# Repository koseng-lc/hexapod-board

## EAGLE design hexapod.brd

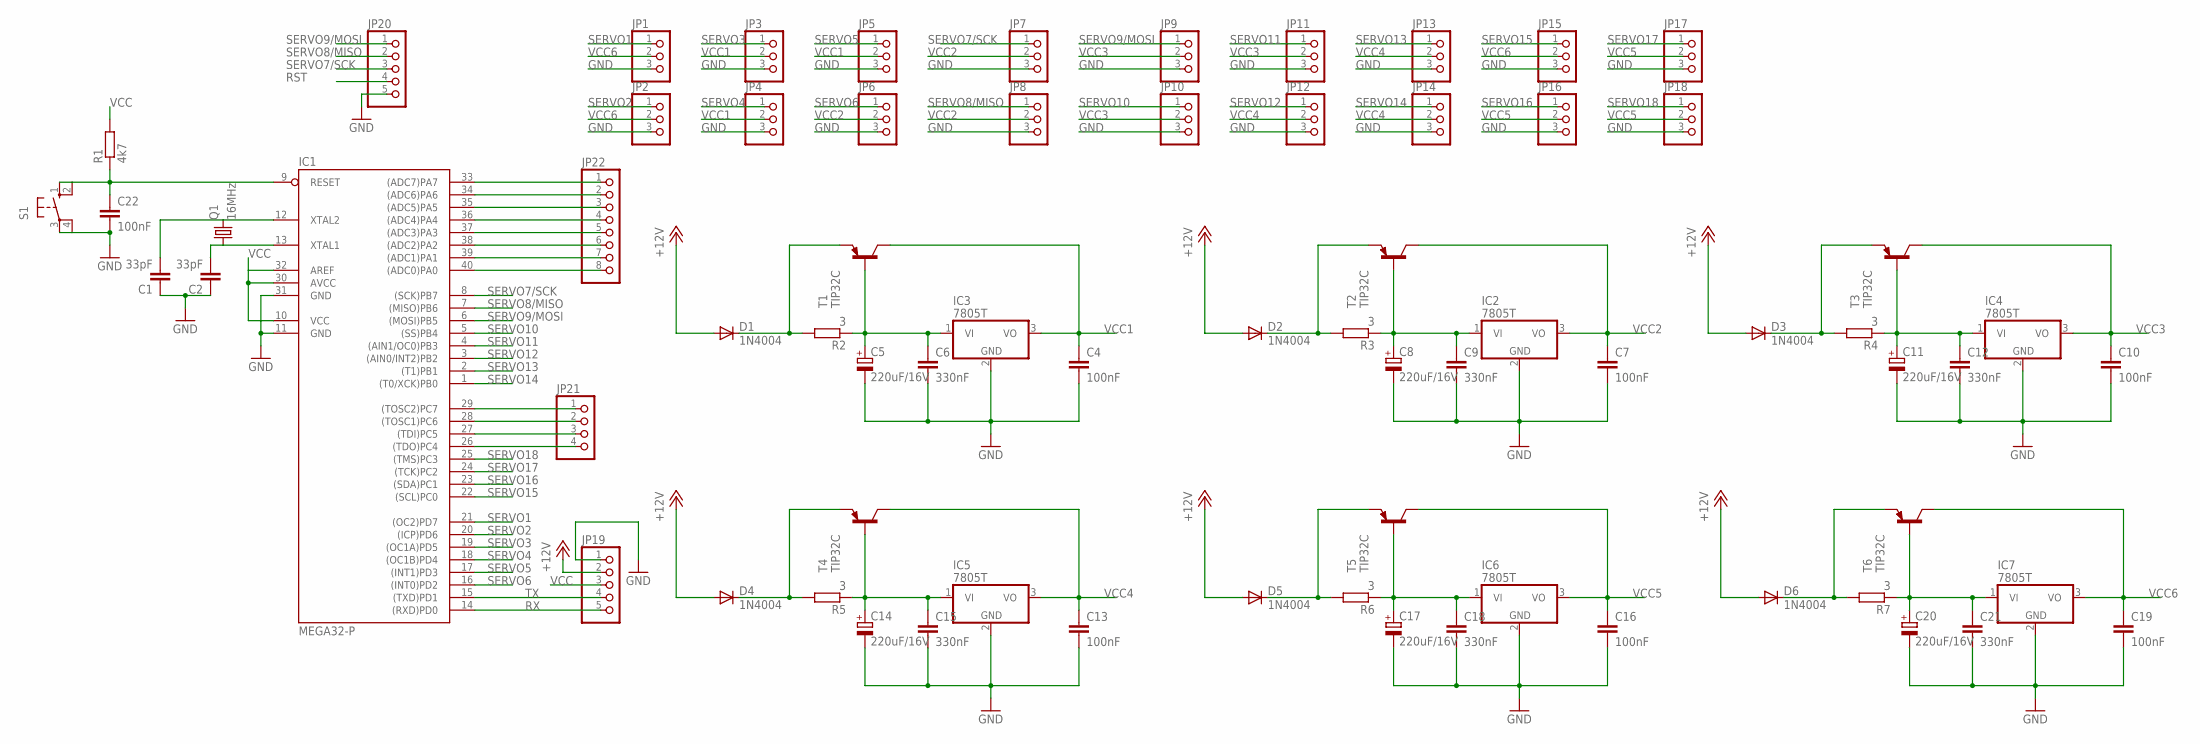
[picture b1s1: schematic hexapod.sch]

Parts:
C1, C2: 33pF; C025-025X050
C4, C7, C10, C13, C16, C19, C22: 100nF; C050-025X075
C5, C8, C11, C14, C17, C20: 220uF/16V; E2,5-6E
C6, C9, C12, C15, C18, C21: 330nF; C050-025X075
D1, D2, D3, D4, D5, D6: 1N4004; DO41-10
IC1: MEGA32-P; DIL40
IC2, IC3, IC4, IC5, IC6, IC7: 7805T; TO220H
JP1, JP2, JP3, JP4, JP5, JP6, JP7, JP8, JP9, JP10, JP11, JP12, JP13, JP14, JP15, JP16, JP17, JP18: PINHD-1X3; 1X03
JP19, JP20: PINHD-1X5; 1X05
JP21: PINHD-1X4; 1X04
JP22: PINHD-1X8; 1X08
Q1: 16MHz; HC49/S
R1: 4k7; 0204/7
R2, R3, R4, R5, R6, R7: 3; 0204/7
S1: 10-XX; B3F-10XX
T1, T2, T3, T4, T5, T6: TIP32C; TO220

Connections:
+12V: D1.A, D2.A, D3.A, D4.A, D5.A, D6.A, JP19.2
GND: C1.1, C2.1, C4.2, C5.-, C6.2, C7.2, C8.-, C9.2, C10.2, C11.-, C12.2, C13.2, C14.-, C15.2, C16.2, C17.-, C18.2, C19.2, C20.-, C21.2, C22.2, IC1.11 (GND), IC1.31 (GND), IC2.2 (GND), IC3.2 (GND), IC4.2 (GND), IC5.2 (GND), IC6.2 (GND), IC7.2 (GND), JP1.3, JP2.3, JP3.3, JP4.3, JP5.3, JP6.3, JP7.3, JP8.3, JP9.3, JP10.3, JP11.3, JP12.3, JP13.3, JP14.3, JP15.3, JP16.3, JP17.3, JP18.3, JP19.1, JP20.5, S1.3, S1.4 (P1)
unnamed: C1.2, IC1.12 (XTAL2), Q1.2
unnamed: C2.2, IC1.13 (XTAL1), Q1.1
unnamed: IC1.40 ((ADC0)PA0), JP22.8
unnamed: IC1.39 ((ADC1)PA1), JP22.7
unnamed: D1.C, R2.2, T1.3 (E)
unnamed: D2.C, R3.2, T2.3 (E)
unnamed: IC1.38 ((ADC2)PA2), JP22.6
unnamed: C5.+, C6.1, IC3.1 (VI), R2.1, T1.1 (B)
unnamed: IC1.29 ((TOSC2)PC7), JP21.1
unnamed: IC1.37 ((ADC3)PA3), JP22.5
unnamed: IC1.36 ((ADC4)PA4), JP22.4
unnamed: IC1.28 ((TOSC1)PC6), JP21.2
unnamed: IC1.35 ((ADC5)PA5), JP22.3
unnamed: IC1.34 ((ADC6)PA6), JP22.2
unnamed: IC1.33 ((ADC7)PA7), JP22.1
unnamed: IC1.27 ((TDI)PC5), JP21.3
unnamed: IC1.26 ((TDO)PC4), JP21.4
unnamed: C8.+, C9.1, IC2.1 (VI), R3.1, T2.1 (B)
unnamed: D3.C, R4.2, T3.3 (E)
unnamed: C11.+, C12.1, IC4.1 (VI), R4.1, T3.1 (B)
unnamed: D4.C, R5.2, T4.3 (E)
unnamed: C14.+, C15.1, IC5.1 (VI), R5.1, T4.1 (B)
unnamed: D5.C, R6.2, T5.3 (E)
unnamed: C17.+, C18.1, IC6.1 (VI), R6.1, T5.1 (B)
unnamed: D6.C, R7.2, T6.3 (E)
unnamed: C20.+, C21.1, IC7.1 (VI), R7.1, T6.1 (B)
RST: C22.1, IC1.9 (RESET), JP20.4, R1.1, S1.1 (S), S1.2 (S1)
RX: IC1.14 ((RXD)PD0), JP19.5
SERVO1: IC1.21 ((OC2)PD7), JP1.1
SERVO2: IC1.20 ((ICP)PD6), JP2.1
SERVO3: IC1.19 ((OC1A)PD5), JP3.1
SERVO4: IC1.18 ((OC1B)PD4), JP4.1
SERVO5: IC1.17 ((INT1)PD3), JP5.1
SERVO6: IC1.16 ((INT0)PD2), JP6.1
SERVO7/SCK: IC1.8 ((SCK)PB7), JP7.1, JP20.3
SERVO8/MISO: IC1.7 ((MISO)PB6), JP8.1, JP20.2
SERVO9/MOSI: IC1.6 ((MOSI)PB5), JP9.1, JP20.1
SERVO10: IC1.5 ((SS)PB4), JP10.1
SERVO11: IC1.4 ((AIN1/OC0)PB3), JP11.1
SERVO12: IC1.3 ((AIN0/INT2)PB2), JP12.1
SERVO13: IC1.2 ((T1)PB1), JP13.1
SERVO14: IC1.1 ((T0/XCK)PB0), JP14.1
SERVO15: IC1.22 ((SCL)PC0), JP15.1
SERVO16: IC1.23 ((SDA)PC1), JP16.1
SERVO17: IC1.24 ((TCK)PC2), JP17.1
SERVO18: IC1.25 ((TMS)PC3), JP18.1
TX: IC1.15 ((TXD)PD1), JP19.4
VCC: IC1.10 (VCC), IC1.30 (AVCC), IC1.32 (AREF), JP19.3, R1.2
VCC1: C4.1, IC3.3 (VO), JP3.2, JP4.2, JP5.2, T1.2 (C)
VCC2: C7.1, IC2.3 (VO), JP6.2, JP7.2, JP8.2, T2.2 (C)
VCC3: C10.1, IC4.3 (VO), JP9.2, JP10.2, JP11.2, T3.2 (C)
VCC4: C13.1, IC5.3 (VO), JP12.2, JP13.2, JP14.2, T4.2 (C)
VCC5: C16.1, IC6.3 (VO), JP16.2, JP17.2, JP18.2, T5.2 (C)
VCC6: C19.1, IC7.3 (VO), JP1.2, JP2.2, JP15.2, T6.2 (C)

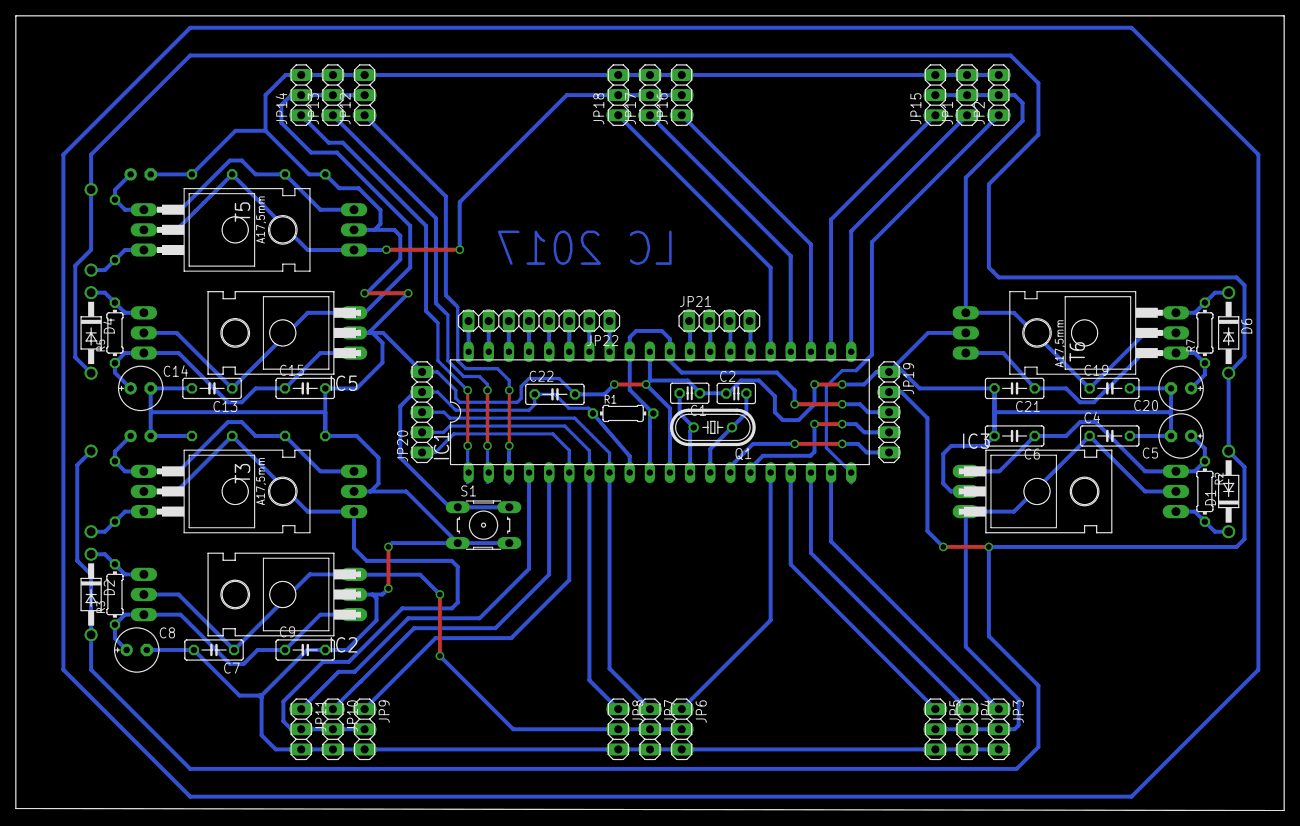
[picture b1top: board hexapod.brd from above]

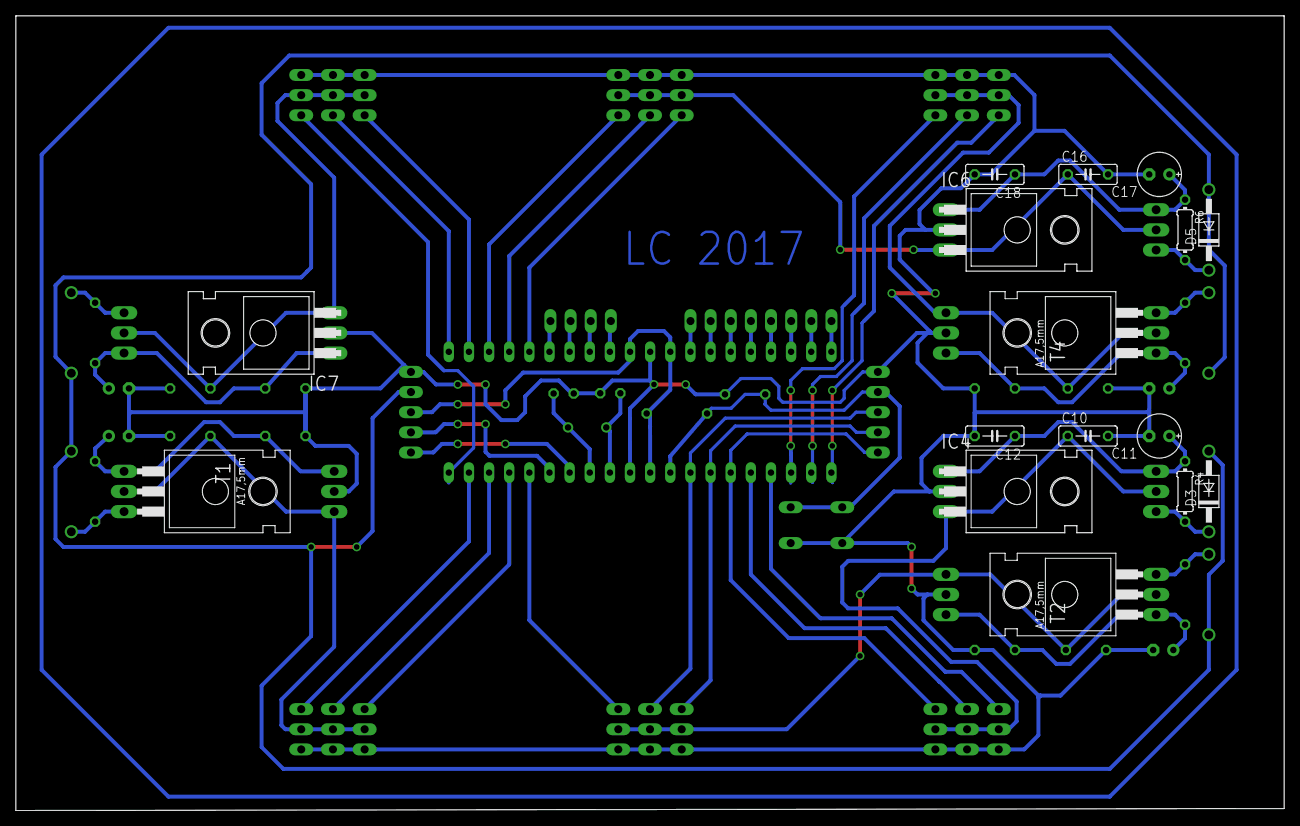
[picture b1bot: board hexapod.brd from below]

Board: 2 copper layers, 160.0 x 100.2 mm, 71 parts (16 on the bottom side), 56 nets.

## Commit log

2019-09-03 pcb layout
